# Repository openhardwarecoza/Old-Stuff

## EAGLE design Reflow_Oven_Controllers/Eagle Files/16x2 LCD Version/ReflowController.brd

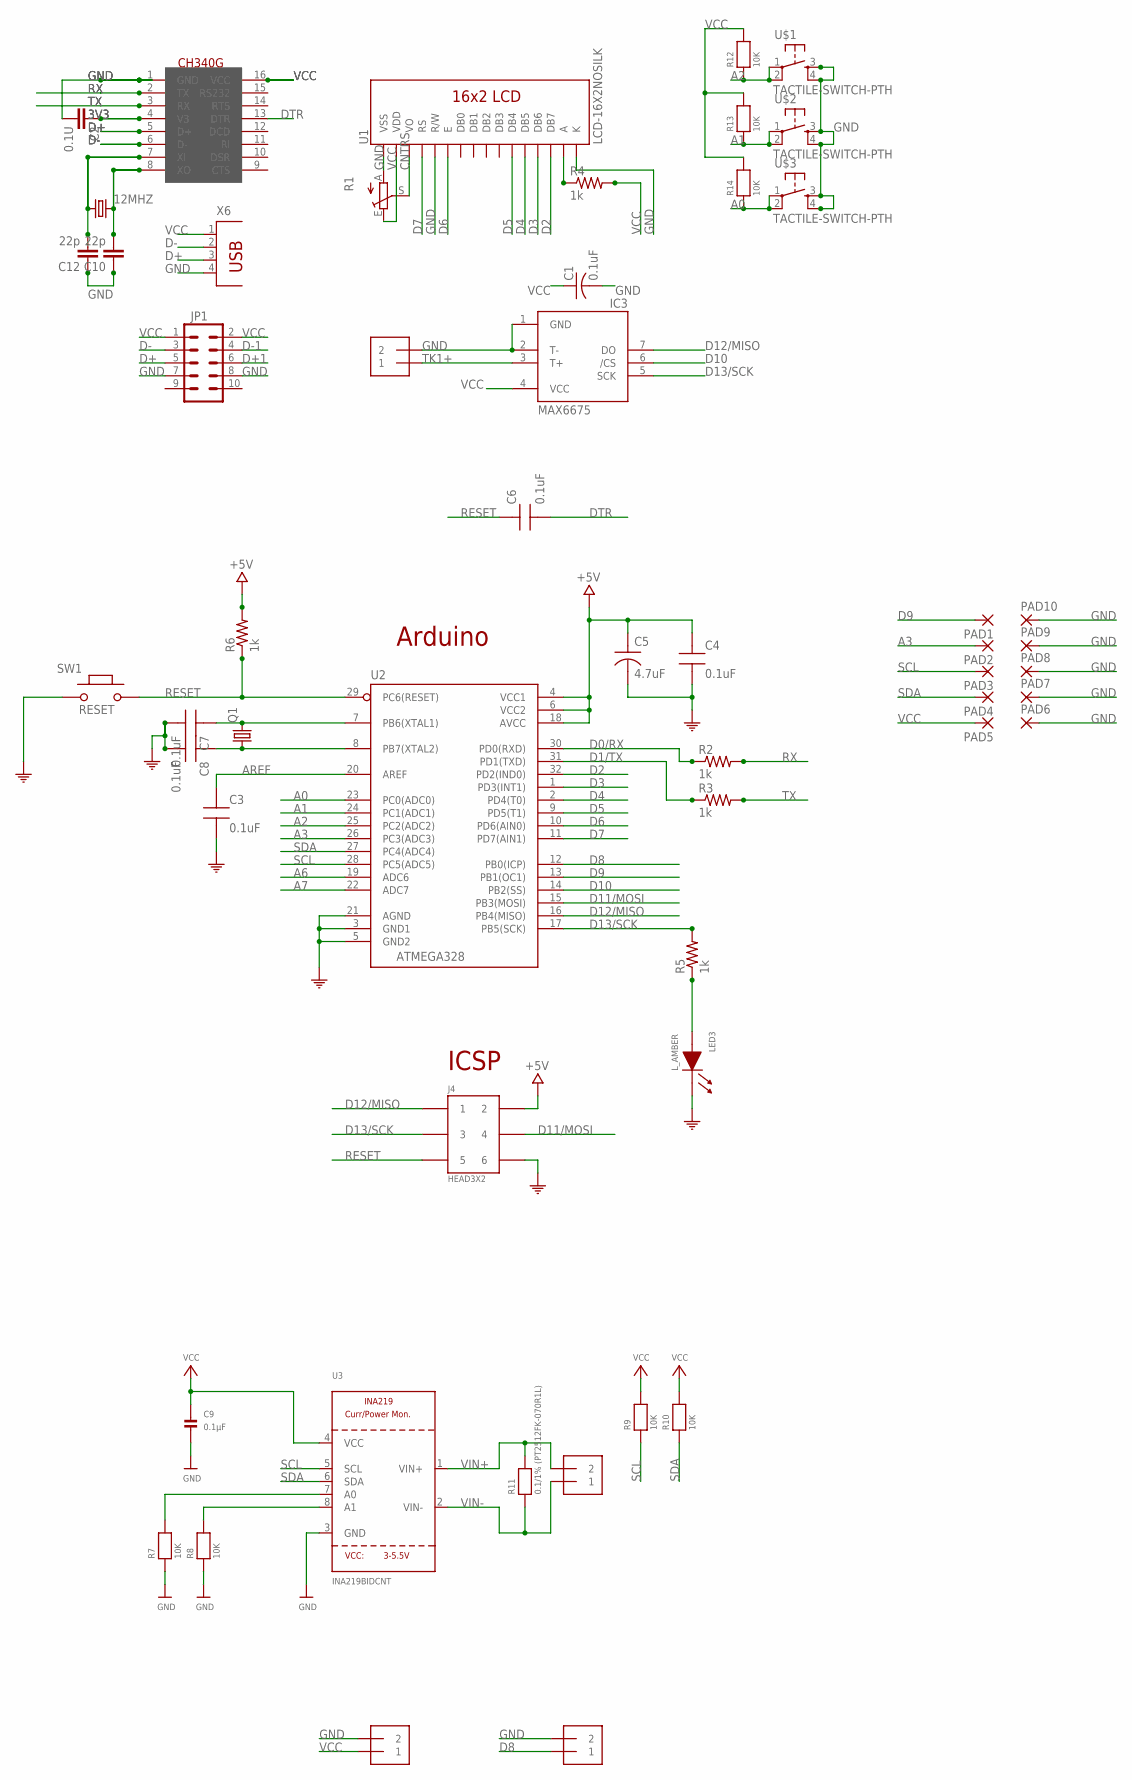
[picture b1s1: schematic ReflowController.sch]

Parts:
12MHZ: CRYSTALHC49UP; HC49UP
C1: 0.1uF; C0805K
C2: 0.1U; C1206
C3, C4, C6, C7, C8: 0.1uF; CAP0805-NP
C5: 4.7uF; TAN-A
C9: 0.1µF; 0805
C10, C12: 22p; C1206
IC3: MAX6675; SO08
J1, J3, J5: TERMBLOCK_1X2-3.5MM; 1X2-3.5MM
J2: 1X2-3.5MM
J4: HEAD3X2
JP1: M05X2SHD_LOCK; 2X5-SHROUDED_LOCK
LED3: L_AMBER; LED0805
PAD1, PAD2, PAD3, PAD4, PAD5, PAD6, PAD7, PAD8, PAD9, PAD10: SMD2; SMD1,27-2,54
Q1: CRYSTALHC49UP; HC49UP
R1: TRIM_EU-CA9V; CA9V
R2, R3, R4, R5, R6: 1k; 1206
R7, R8, R9, R10, R12, R13, R14: 10K; 0805
R11: 0.1/1% (PT2512FK-070R1L); 2512
SW1: RESET; 157SW
U1: LCD-16X2NOSILK; LCD-16X2_NOSILK
U2: ATMEGA328; QFP032
U3: INA219BIDCNT; SOT23-8
U$1, U$2, U$3: TACTILE-SWITCH-PTH; TAC-SWITCH-PTH
U$4: CH340G; SOIC16
X6: PN61729

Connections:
3V3: C2.1, U$4.4 (V3)
A0: R14.1, U2.23 (PC0(ADC0)), U$3.1, U$3.2
A1: R13.1, U2.24 (PC1(ADC1)), U$2.1, U$2.2
A2: R12.1, U2.25 (PC2(ADC2)), U$1.1, U$1.2
A3: PAD2.1, U2.26 (PC3(ADC3))
A6: U2.19 (ADC6)
A7: U2.22 (ADC7)
AREF: C3.1, U2.20 (AREF)
CNTRS: R1.S, U1.3 (VO)
D0/RX: R2.1, U2.30 (PD0(RXD))
D1/TX: R3.1, U2.31 (PD1(TXD))
D2: U1.14 (DB7), U2.32 (PD2(IND0))
D3: U1.13 (DB6), U2.1 (PD3(INT1))
D4: U1.12 (DB5), U2.2 (PD4(T0))
D5: U1.11 (DB4), U2.9 (PD5(T1))
D6: U1.6 (E), U2.10 (PD6(AIN0))
D7: U1.4 (RS), U2.11 (PD7(AIN1))
D8: J3.1, U2.12 (PB0(ICP))
D9: PAD1.1, U2.13 (PB1(OC1))
D10: IC3.6 (/CS), U2.14 (PB2(SS))
D11/MOSI: J4.4, U2.15 (PB3(MOSI))
D12/MISO: IC3.7 (DO), J4.1, U2.16 (PB4(MISO))
D13/SCK: IC3.5 (SCK), J4.3, R5.2, U2.17 (PB5(SCK))
D+: JP1.5, U$4.5 (D+), X6.3
D+1: JP1.6
D-: JP1.3, U$4.6 (D-), X6.2
D-1: JP1.4
DTR: C6.2, U$4.13 (DTR)
GND: C1.2, C2.2, C3.2, C4.2, C5.2, C7.2, C8.2, C9.2, C10.1, C12.1, IC3.1 (GND), IC3.2 (T-), J2.2, J3.2, J4.6, J5.2, JP1.7, JP1.8, LED3.1 (CA), PAD6.1, PAD7.1, PAD8.1, PAD9.1, PAD10.1, R1.A, R7.1, R8.1, SW1.1, U1.1 (VSS), U1.5 (R/W), U1.16 (K), U2.3 (GND1), U2.5 (GND2), U2.21 (AGND), U3.3 (GND), U$1.3, U$1.4, U$2.3, U$2.4, U$3.3, U$3.4, U$4.1 (GND), X6.4
unnamed: C8.1, Q1.1, U2.8 (PB7(XTAL2))
unnamed: C7.1, Q1.2, U2.7 (PB6(XTAL1))
unnamed: R8.2, U3.8 (A1)
unnamed: R7.2, U3.7 (A0)
unnamed: LED3.2 (AN), R5.1
unnamed: R4.1, U1.15 (A)
unnamed: 12MHZ.1, C12.2, U$4.7 (XI)
unnamed: 12MHZ.2, C10.2, U$4.8 (XO)
RESET: C6.1, J4.5, R6.1, SW1.2, U2.29 (PC6(RESET))
RX: R2.2, U$4.2 (TX)
SCL: PAD3.1, R9.1, U2.28 (PC5(ADC5)), U3.5 (SCL)
SDA: PAD4.1, R10.1, U2.27 (PC4(ADC4)), U3.6 (SDA)
TK1+: IC3.3 (T+), J2.1
TX: R3.2, U$4.3 (RX)
VCC: C1.1, C4.1, C5.1, C9.1, IC3.4 (VCC), J4.2, J5.1, JP1.1, JP1.2, PAD5.1, R1.E, R4.2, R6.2, R9.2, R10.2, R12.2, R13.2, R14.2, U1.2 (VDD), U2.4 (VCC1), U2.6 (VCC2), U2.18 (AVCC), U3.4 (VCC), U$4.16 (VCC), X6.1
VIN+: J1.2, R11.2, U3.1 (VIN+)
VIN-: J1.1, R11.1, U3.2 (VIN-)

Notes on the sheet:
Arduino
ICSP

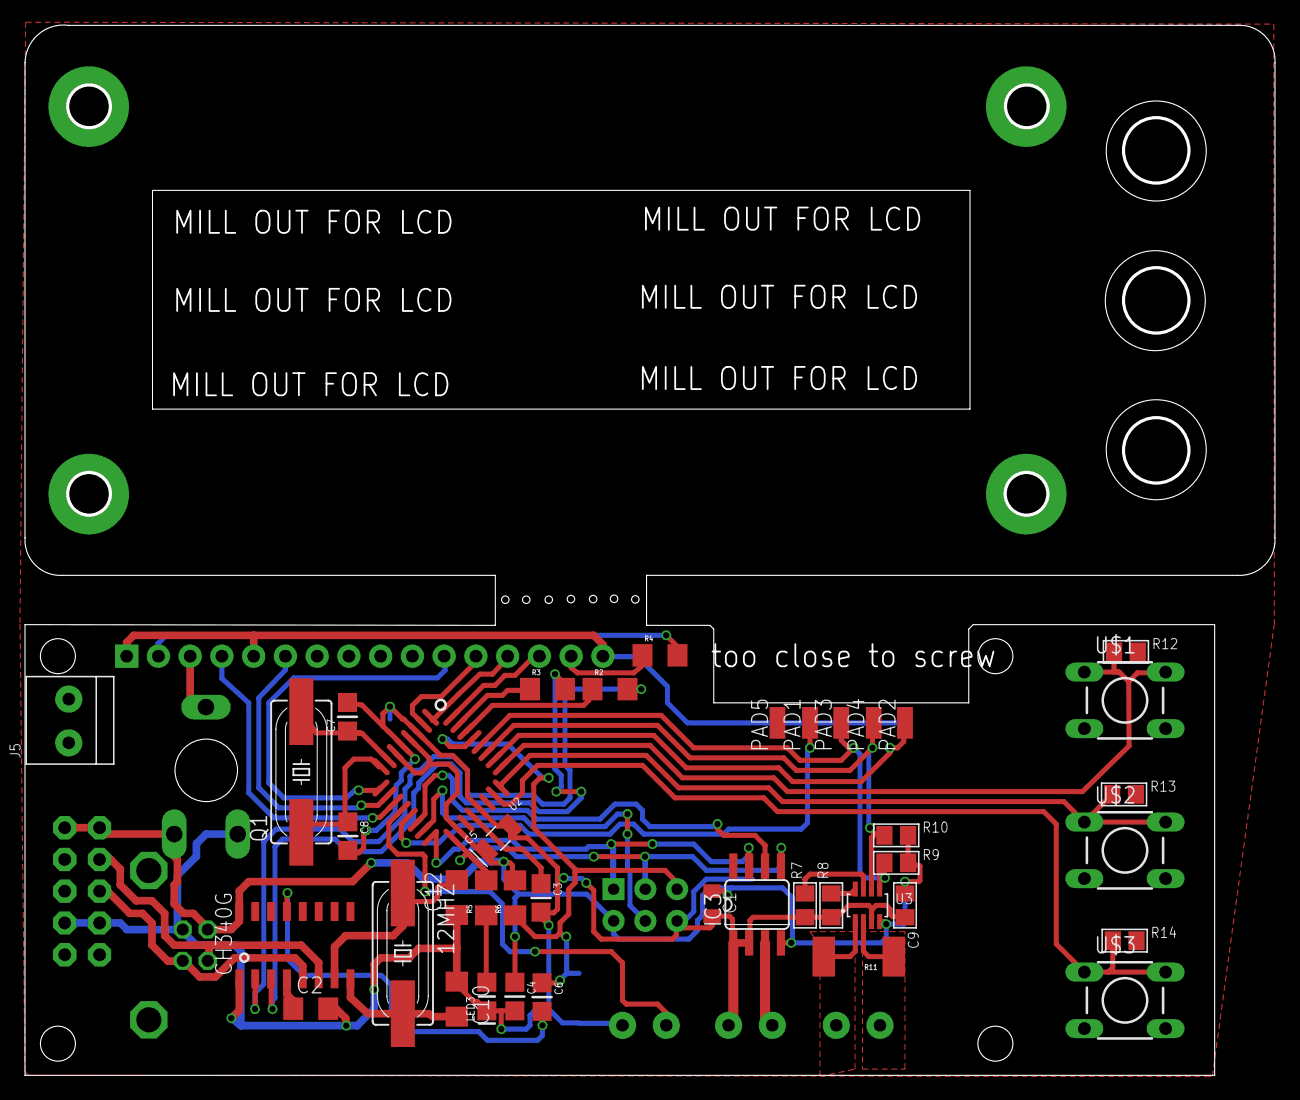
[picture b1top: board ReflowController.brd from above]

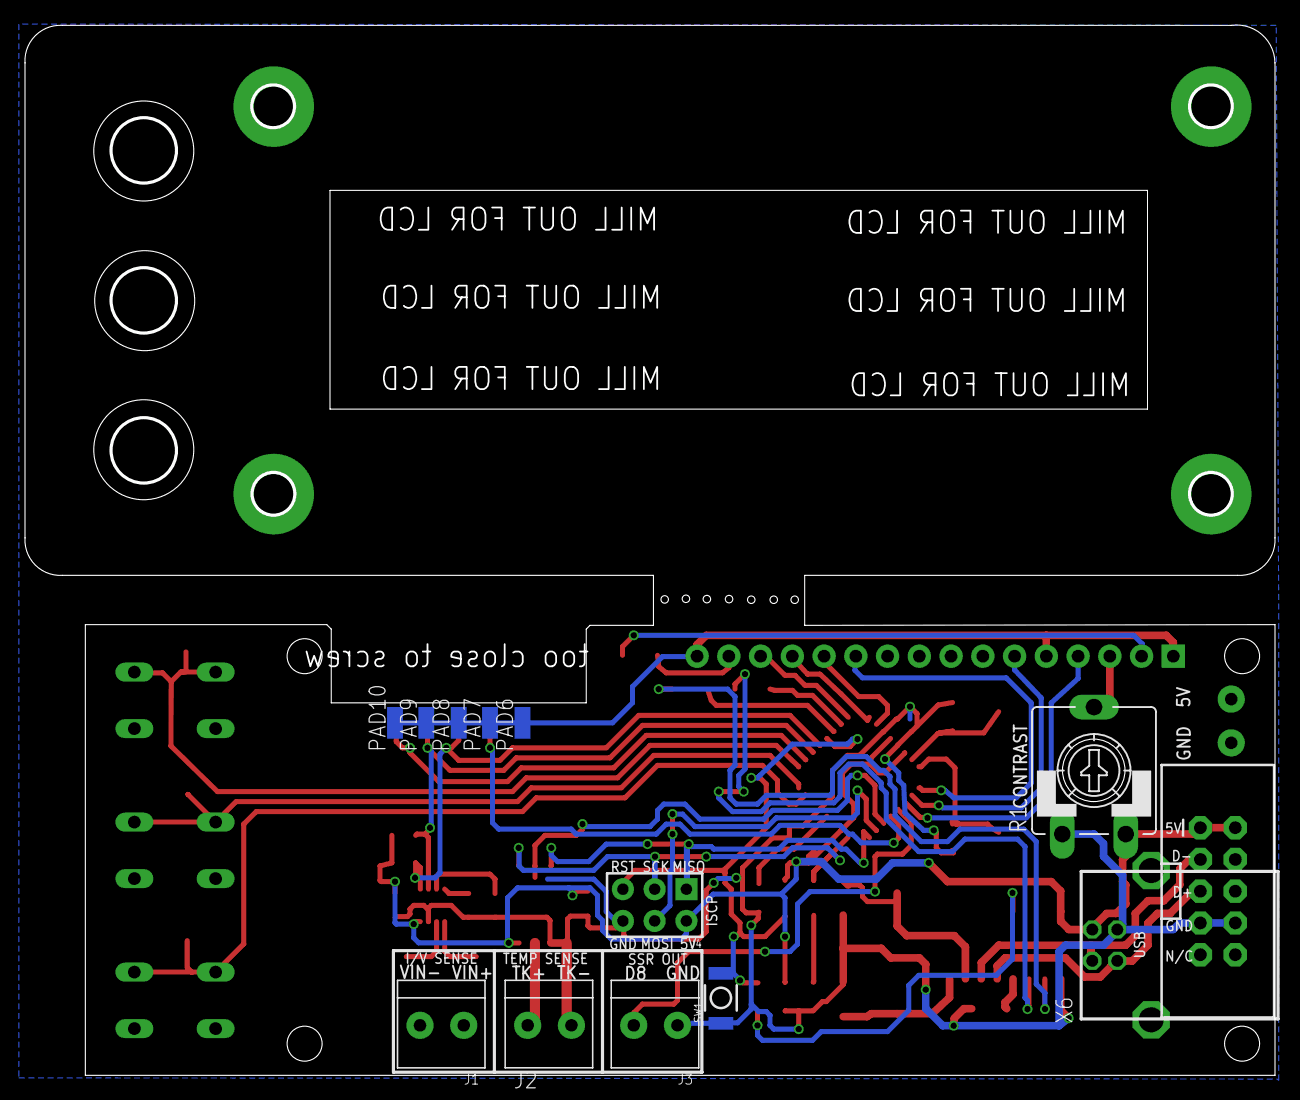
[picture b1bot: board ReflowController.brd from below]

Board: 2 copper layers, 100.0 x 84.0 mm, 54 parts (13 on the bottom side), 42 nets.

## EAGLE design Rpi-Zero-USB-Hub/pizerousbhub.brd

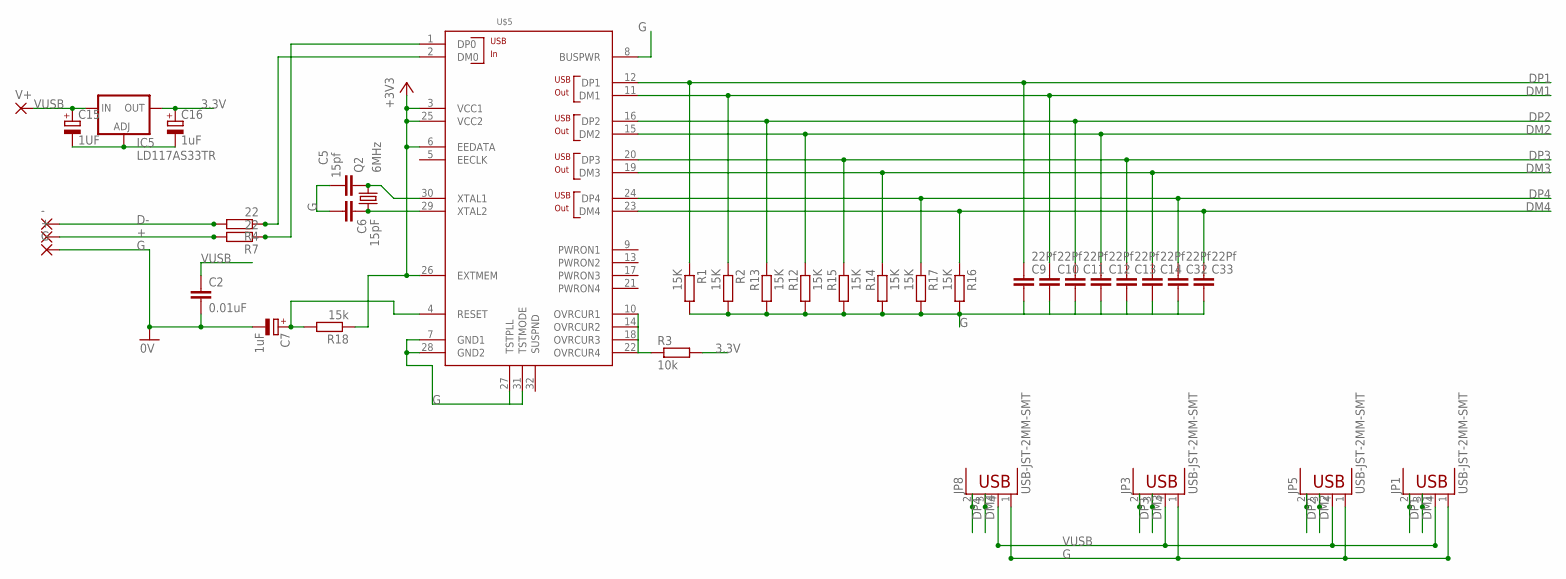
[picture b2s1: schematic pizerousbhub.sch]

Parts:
+: SMD2; SMD1,27-2,54
-: SMD2; SMD1,27-2,54
C2: 0.01uF; C0603
C5: 15pf; C0603
C6: 15pF; C0603
C7: 1uF; A/3216-18W
C9, C10, C11, C12, C13, C14, C32, C33: 22Pf; C0603
C15: 1UF; A/3216-18W
C16: 1uF; C/6032-28R
G: SMD2; SMD1,27-2,54
IC5: LD117AS33TR; SOT223
JP1, JP3, JP5, JP8: USB-JST-2MM-SMT; S4B-PH
Q2: 6MHz; CTS406
R1, R2, R12, R13, R14, R15, R16, R17: 15K; R0603
R3: 10k; R0603
R4, R7: 22; R0603
R18: 15k; R0603
U$5: TUSB2046; LQFP-32
V+: SMD2; SMD1,27-2,54

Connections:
3.3V: C16.+, IC5.4 (OUT), R3.2, R18.1, U$5.3 (VCC1), U$5.6 (EEDATA), U$5.25 (VCC2), U$5.26 (EXTMEM)
+: +.1, R7.2
D-: -.1, R4.2
DM0: R4.1, U$5.2 (DM0)
DM1: C10.1, JP1.3 (D-), R2.1, U$5.11 (DM1)
DM2: C12.1, JP5.3 (D-), R12.1, U$5.15 (DM2)
DM3: C14.1, JP3.3 (D-), R14.1, U$5.19 (DM3)
DM4: C33.1, JP8.3 (D-), R16.1, U$5.23 (DM4)
DP0: R7.1, U$5.1 (DP0)
DP1: C9.1, JP1.2 (D+), R1.1, U$5.12 (DP1)
DP2: C11.1, JP5.2 (D+), R13.1, U$5.16 (DP2)
DP3: C13.1, JP3.2 (D+), R15.1, U$5.20 (DP3)
DP4: C32.1, JP8.2 (D+), R17.1, U$5.24 (DP4)
G: C2.2, C5.1, C6.2, C7.-, C9.2, C10.2, C11.2, C12.2, C13.2, C14.2, C15.-, C16.-, C32.2, C33.2, G.1, IC5.1 (ADJ), JP1.1 (GND), JP3.1 (GND), JP5.1 (GND), JP8.1 (GND), R1.2, R2.2, R12.2, R13.2, R14.2, R15.2, R16.2, R17.2, U$5.7 (GND1), U$5.8 (BUSPWR), U$5.27 (TSTPLL), U$5.28 (GND2), U$5.31 (TSTMODE)
unnamed: R3.1, U$5.10 (OVRCUR1), U$5.14 (OVRCUR2), U$5.18 (OVRCUR3), U$5.22 (OVRCUR4)
RESET: C7.+, R18.2, U$5.4 (RESET)
VUSB: C2.1, C15.+, IC5.3 (IN), JP1.4 (VBUS), JP3.4 (VBUS), JP5.4 (VBUS), JP8.4 (VBUS), V+.1
XTAL1: C5.2, Q2.3 (2), U$5.30 (XTAL1)
XTAL2: C6.1, Q2.1, U$5.29 (XTAL2)

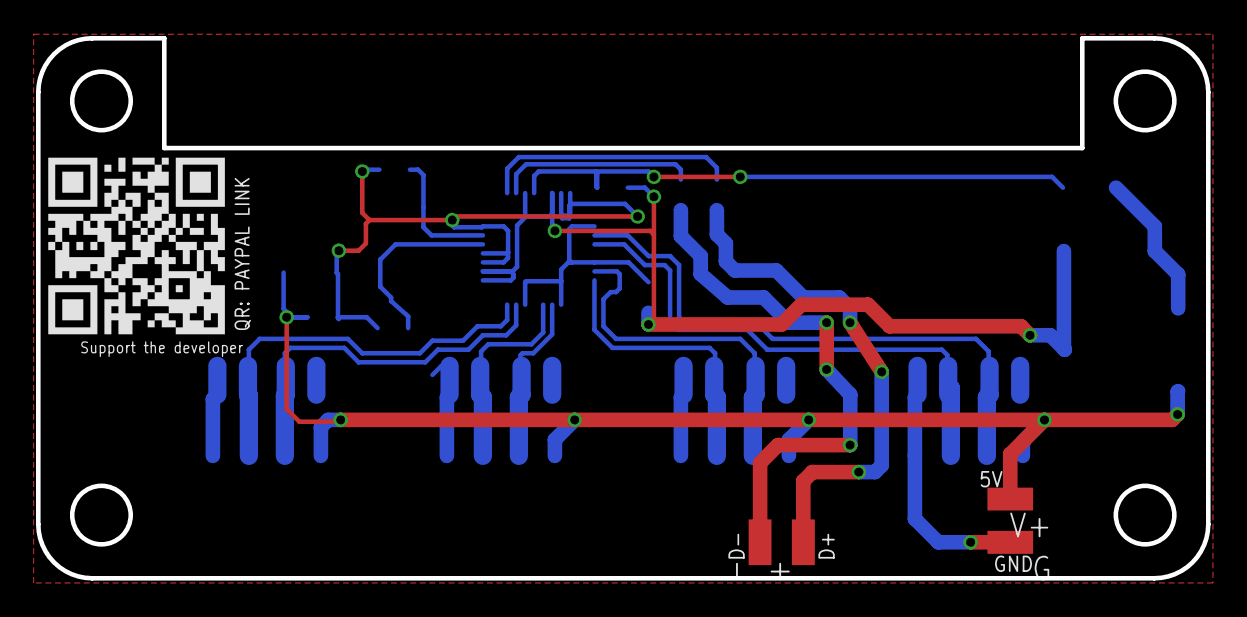
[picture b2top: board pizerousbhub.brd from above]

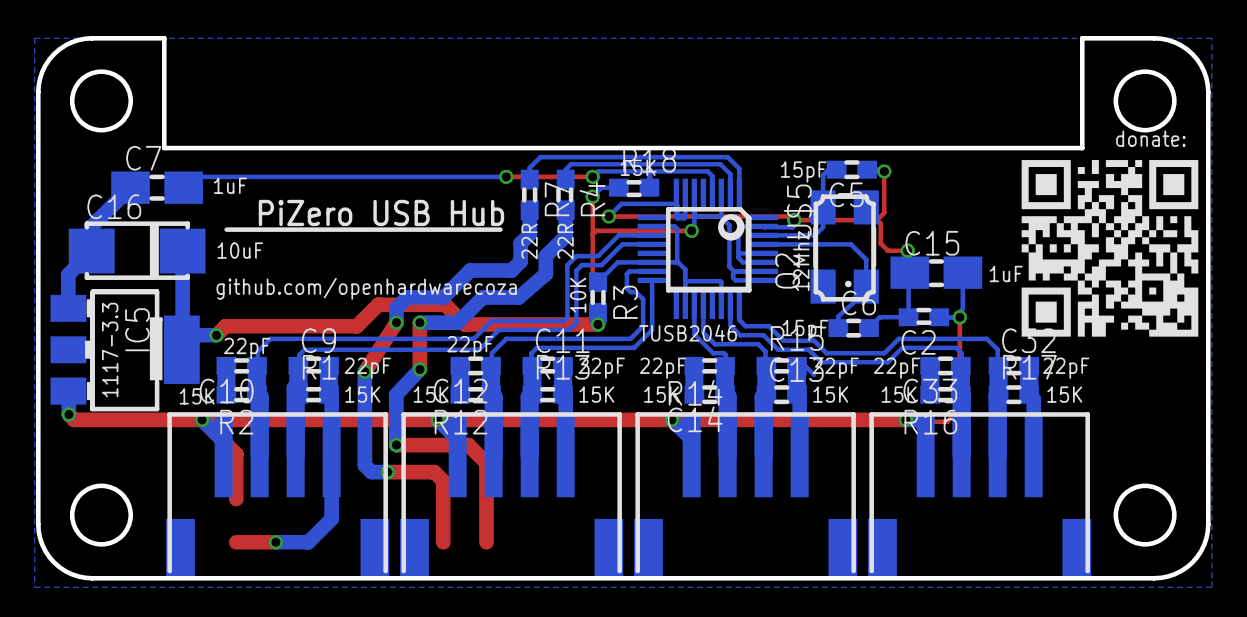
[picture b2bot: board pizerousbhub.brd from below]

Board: 2 copper layers, 65.0 x 30.0 mm, 37 parts (33 on the bottom side), 19 nets.

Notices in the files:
parts and their libraries:
SparkFun-Displays: Licensing: Creative Commons ShareAlike 4.0 International - https://creativecommons.org/licenses/by-sa/4.0
SparkFun-Connectors_PETERMICROSDEBAY: Licensing: CC v3.0 Share-Alike You are welcome to use this library for commercial purposes.
rc-master-smd: Copyright (C) 2007, Bob Starr
